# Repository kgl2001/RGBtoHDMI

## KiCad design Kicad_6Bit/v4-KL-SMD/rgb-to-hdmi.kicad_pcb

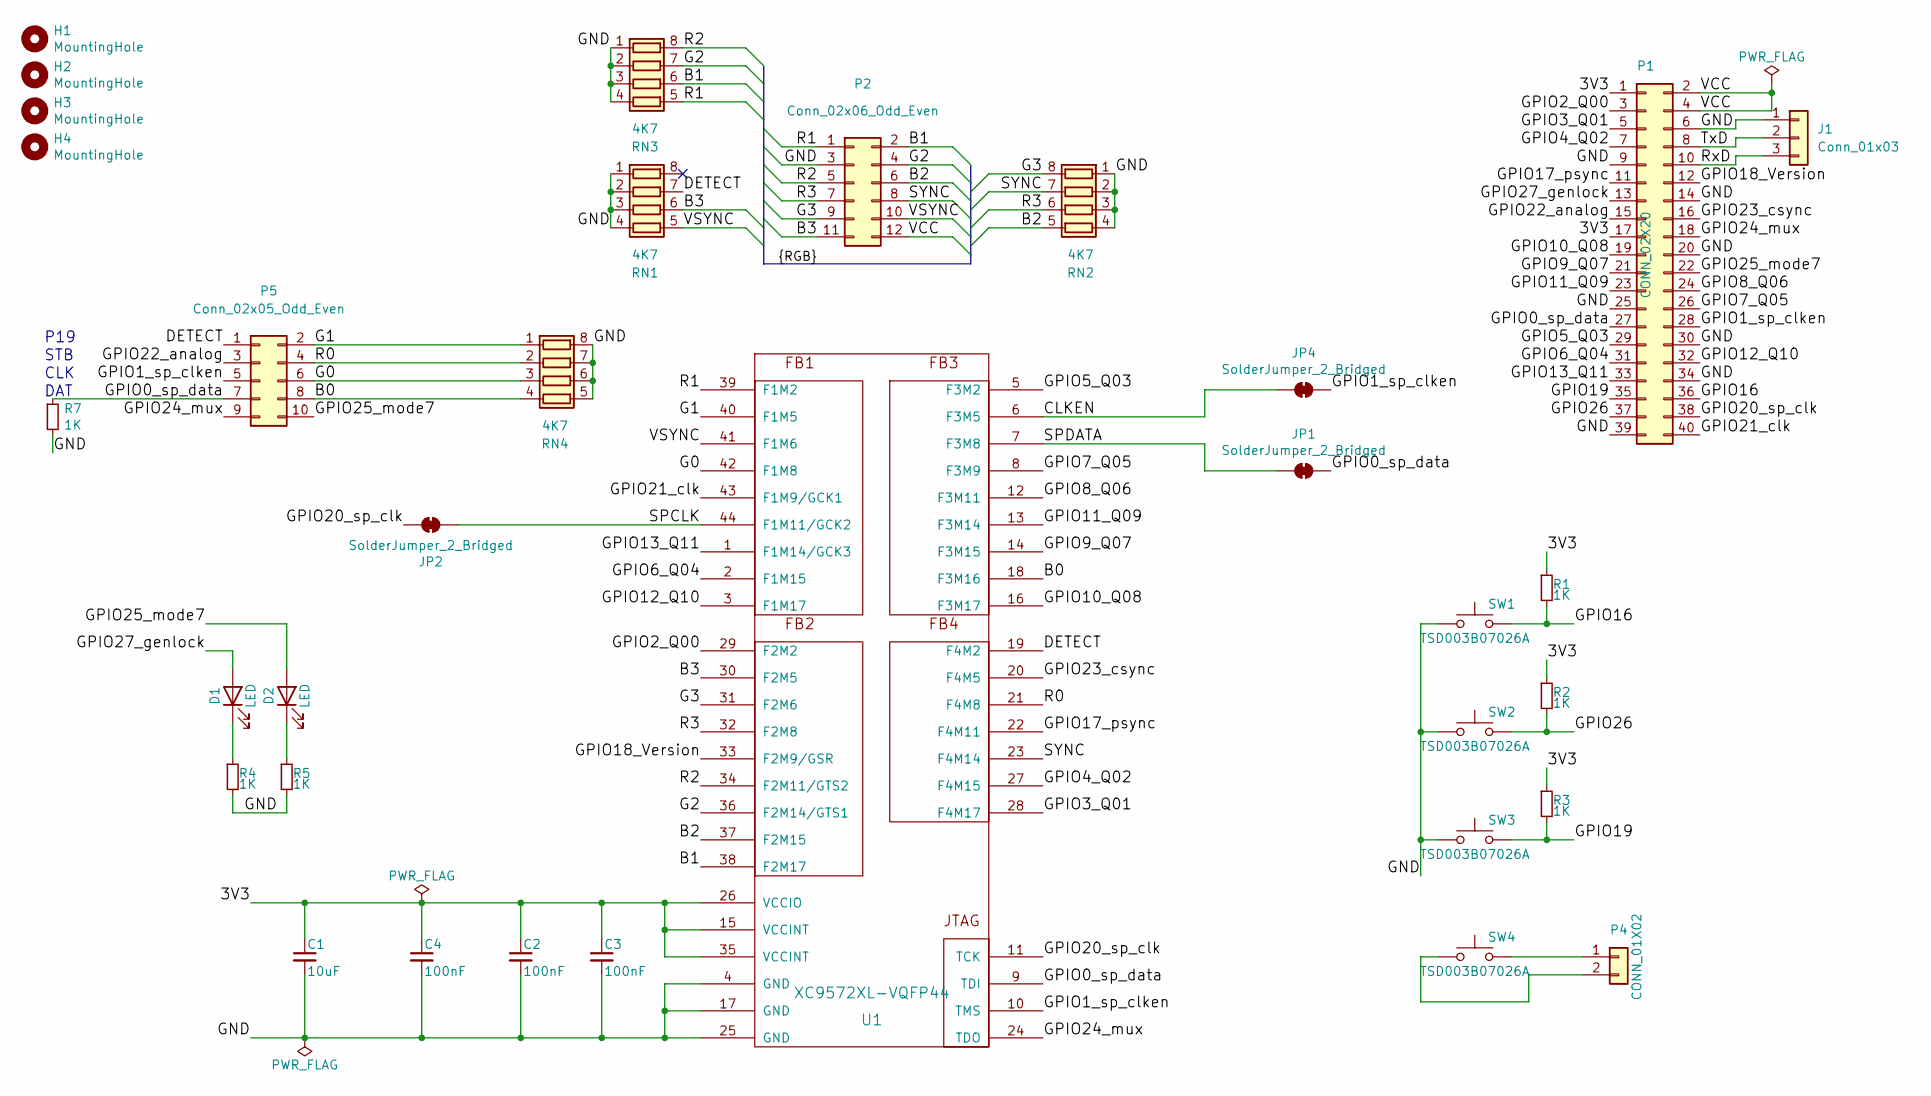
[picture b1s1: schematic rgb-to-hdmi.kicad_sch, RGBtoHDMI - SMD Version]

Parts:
C1: 10uF; C_0805_2012Metric; JLC Part Number C15850
C2, C3, C4: 100nF; C_0805_2012Metric; JLC Part Number C49678
D1, D2: LED; LED_0603_1608Metric; JLC Part Number C72043
H1, H2, H3, H4: MountingHole; MountingHole_2.7mm_M2.5_DIN965
J1: Conn_01x03; PinHeader_1x03_P2.54mm_Vertical
JP1, JP2, JP4: SolderJumper_2_Bridged; SolderJumper-2_P1.3mm_Bridged_RoundedPad1.0x1.5mm
P1: CONN_02X20; PinSocket_2x20_P2.54mm_Vertical
P2: Conn_02x06_Odd_Even; PinHeader_2x06_P2.54mm_Horizontal
P4: CONN_01X02; PinSocket_1x02_P2.54mm_Vertical
P5: Conn_02x05_Odd_Even; PinSocket_2x05_P2.54mm_Vertical
R1, R2, R3, R4, R5, R7: 1K; R_0603_1608Metric; JLC Part Number C21190
RN1, RN2, RN3, RN4: 4K7; R_Array_Concave_4x0603; JLC Part Number C1980
SW1, SW2, SW3, SW4: TSD003B07026A; SW_SPST_PTS645; JLC Part Number C2888790
U1: XC9572XL-VQFP44; LQFP-44_10x10mm_P0.8mm; JLC Part Number C569042

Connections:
/3V3: C1.1, C2.1, C3.1, C4.1, P1.1, P1.17, R1.1, R2.1, R3.1, U1.15 (VCCINT), U1.26 (VCCIO), U1.35 (VCCINT)
/B0: P5.8, RN4.4 (R4.1), U1.18 (F3M16)
/B1: P2.2, RN3.6 (R3.2), U1.38 (F2M17)
/B2: P2.6, RN2.5 (R4.2), U1.37 (F2M15)
/B3: P2.11, RN1.6 (R3.2), U1.30 (F2M5)
/CLKEN: JP4.2 (B), U1.6 (F3M5)
/DETECT: P5.1, RN1.7 (R2.2), U1.19 (F4M2)
/G0: P5.6, RN4.3 (R3.1), U1.42 (F1M8)
/G1: P5.2, RN4.1 (R1.1), U1.40 (F1M5)
/G2: P2.4, RN3.7 (R2.2), U1.36 (F2M14/GTS1)
/G3: P2.9, RN2.8 (R1.2), U1.31 (F2M6)
/GND: C1.2, C2.2, C3.2, C4.2, J1.1, P1.6, P1.9, P1.14, P1.20, P1.25, P1.30, P1.34, P1.39, P2.3, R4.2, R5.2, R7.2, RN1.1 (R1.1), RN1.2 (R2.1), RN1.3 (R3.1), RN1.4 (R4.1), RN2.1 (R1.1), RN2.2 (R2.1), RN2.3 (R3.1), RN2.4 (R4.1), RN3.1 (R1.1), RN3.2 (R2.1), RN3.3 (R3.1), RN3.4 (R4.1), RN4.5 (R4.2), RN4.6 (R3.2), RN4.7 (R2.2), RN4.8 (R1.2), SW1.1, SW2.1, SW3.1, U1.4 (GND), U1.17 (GND), U1.25 (GND)
/GPIO0_sp_data: JP1.1 (A), P1.27, P5.7, R7.1, U1.9 (TDI)
/GPIO1_sp_clken: JP4.1 (A), P1.28, P5.5, U1.10 (TMS)
/GPIO2_Q00: P1.3, U1.29 (F2M2)
/GPIO3_Q01: P1.5, U1.28 (F4M17)
/GPIO4_Q02: P1.7, U1.27 (F4M15)
/GPIO5_Q03: P1.29, U1.5 (F3M2)
/GPIO6_Q04: P1.31, U1.2 (F1M15)
/GPIO7_Q05: P1.26, U1.8 (F3M9)
/GPIO8_Q06: P1.24, U1.12 (F3M11)
/GPIO9_Q07: P1.21, U1.14 (F3M15)
/GPIO10_Q08: P1.19, U1.16 (F3M17)
/GPIO11_Q09: P1.23, U1.13 (F3M14)
/GPIO12_Q10: P1.32, U1.3 (F1M17)
/GPIO13_Q11: P1.33, U1.1 (F1M14/GCK3)
/GPIO16: P1.36, R1.2, SW1.2
/GPIO17_psync: P1.11, U1.22 (F4M11)
/GPIO18_Version: P1.12, U1.33 (F2M9/GSR)
/GPIO19: P1.35, R3.2, SW3.2
/GPIO20_sp_clk: JP2.1 (A), P1.38, U1.11 (TCK)
/GPIO21_clk: P1.40, U1.43 (F1M9/GCK1)
/GPIO22_analog: P1.15, P5.3
/GPIO23_csync: P1.16, U1.20 (F4M5)
/GPIO24_mux: P1.18, P5.9, U1.24 (TDO)
/GPIO25_mode7: D2.2 (A), P1.22, P5.10
/GPIO26: P1.37, R2.2, SW2.2
/GPIO27_genlock: D1.2 (A), P1.13
/R0: P5.4, RN4.2 (R2.1), U1.21 (F4M8)
/R1: P2.1, RN3.5 (R4.2), U1.39 (F1M2)
/R2: P2.5, RN3.8 (R1.2), U1.34 (F2M11/GTS2)
/R3: P2.7, RN2.6 (R3.2), U1.32 (F2M8)
/RxD: J1.3, P1.10
/SPCLK: JP2.2 (B), U1.44 (F1M11/GCK2)
/SPDATA: JP1.2 (B), U1.7 (F3M8)
/SYNC: P2.8, RN2.7 (R2.2), U1.23 (F4M14)
/TxD: J1.2, P1.8
/VCC: P1.2, P1.4, P2.12
/VSYNC: P2.10, RN1.5 (R4.2), U1.41 (F1M6)
unnamed: D1.1 (K), R4.1
unnamed: D2.1 (K), R5.1
unnamed: P4.1, SW4.2
unnamed: P4.2, SW4.1

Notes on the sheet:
P19
DAT
CLK
STB

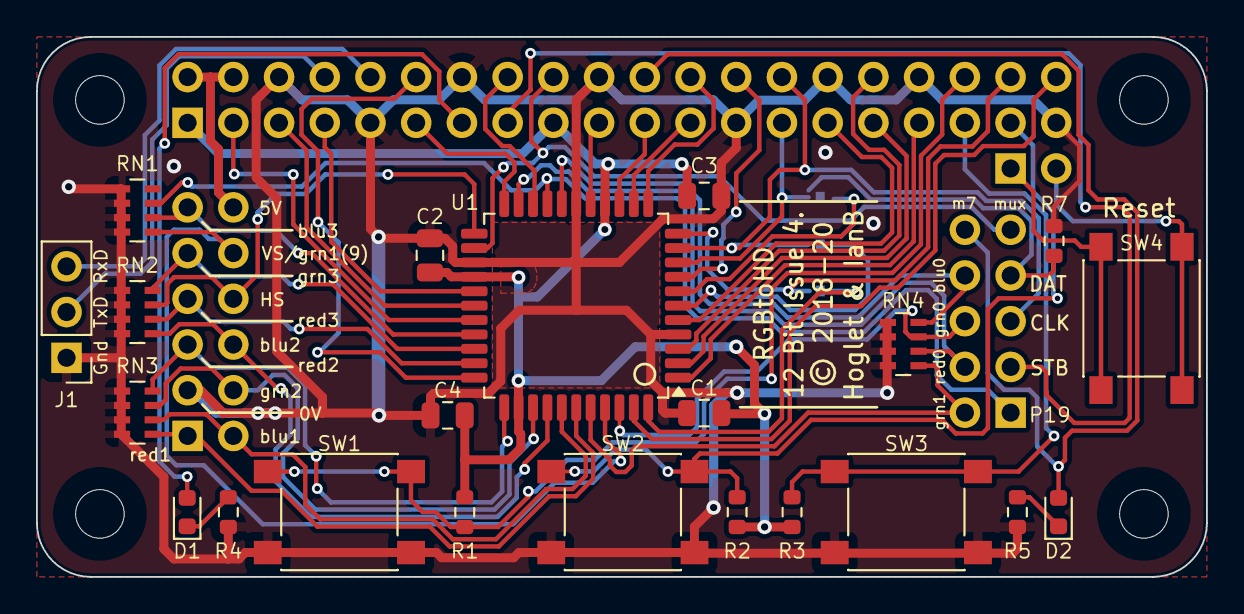
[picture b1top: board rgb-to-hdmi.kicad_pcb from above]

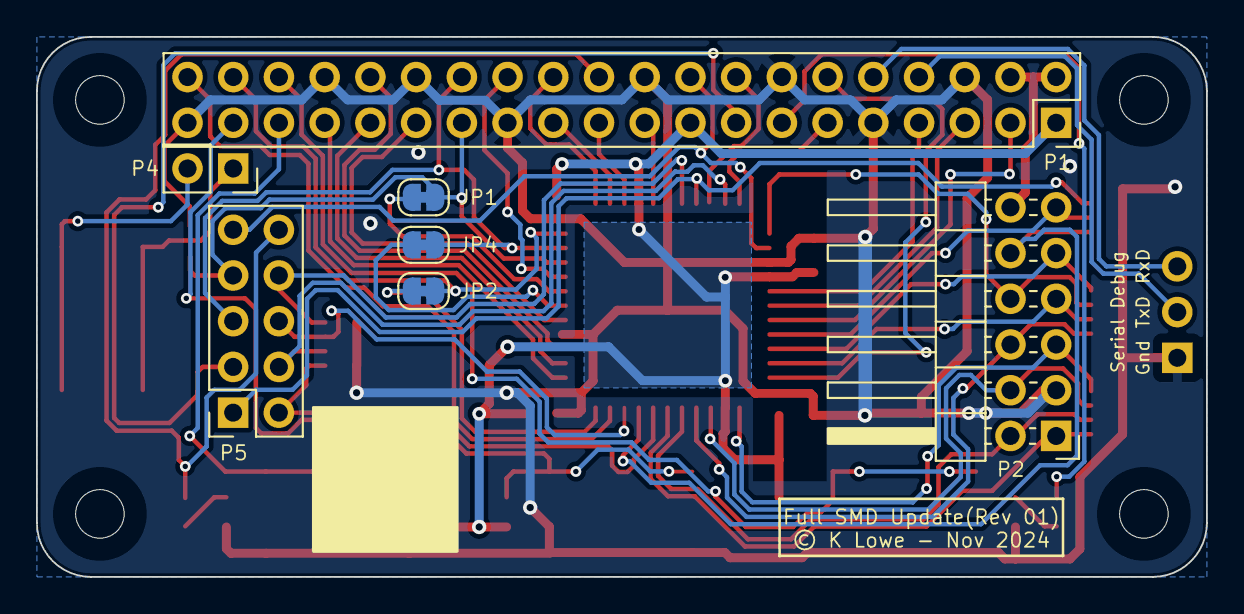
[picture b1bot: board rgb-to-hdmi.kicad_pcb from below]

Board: 2 copper layers, 65.0 x 30.0 mm, 33 parts (7 on the bottom side), 53 nets.

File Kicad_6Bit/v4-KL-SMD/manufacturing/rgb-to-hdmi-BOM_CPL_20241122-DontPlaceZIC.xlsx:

Designator | LCSC Part # | Footprint | JLCValue | Mid X | Mid Y | Rot | Side | Val | Package
C1 | C15850 | 0805 | 10uF | 53.073999999999998 | -45.39996 | 180 | top | 10uF | C_0805_2012Metric
C2 | C49678 | 0805 | 100nF | 37.834000000000003 | -36.636960000000002 | 90 | top | 100nF | C_0805_2012Metric
C3 | C49678 | 0805 | 100nF | 53.073999999999998 | -33.334960000000002 | 0 | top | 100nF | C_0805_2012Metric
C4 | C49678 | 0805 | 100nF | 38.819600000000001 | -45.526960000000003 | 180 | top | 100nF | C_0805_2012Metric
D1 | C72043 | LED_0603 | Green | 24.349 | -50.900959999999998 | 90 | top | LED | LED_0603_1608Metric
D2 | C72043 | LED_0603 | Green | 72.759 | -50.900959999999998 | 90 | top | LED | LED_0603_1608Metric
R1 | C21190 | 0603 | 1K | 39.769599999999997 | -50.900959999999998 | -90 | top | 1K | R_0603_1608Metric
R2 | C21190 | 0603 | 1K | 54.904000000000003 | -50.900959999999998 | 90 | top | 1K | R_0603_1608Metric
R3 | C21190 | 0603 | 1K | 57.951999999999998 | -50.900959999999998 | 90 | top | 1K | R_0603_1608Metric
R4 | C21190 | 0603 | 1K | 26.635000000000002 | -50.900959999999998 | -90 | top | 1K | R_0603_1608Metric
R5 | C21190 | 0603 | 1K | 70.472999999999999 | -50.900959999999998 | -90 | top | 1K | R_0603_1608Metric
R7 | C21190 | 0603 | 1K | 72.507660000000001 | -35.836860000000001 | 90 | top | 1K | R_0603_1608Metric
RN1 | C1980 | 0603_x4 | 4K7 | 21.583200000000001 | -34.141559999999998 | 270 | top | 4K7 | R_Array_Concave_4x0603
RN2 | C1980 | 0603_x4 | 4K7 | 21.583200000000001 | -39.786560000000001 | 270 | top | 4K7 | R_Array_Concave_4x0603
RN3 | C1980 | 0603_x4 | 4K7 | 21.583200000000001 | -45.374560000000002 | 270 | top | 4K7 | R_Array_Concave_4x0603
RN4 | C1980 | 0603_x4 | 4K7 | 64.128200000000007 | -41.56456 | 90 | top | 4K7 | R_Array_Concave_4x0603
SW1 | C2888790 | SMD | TSD003B07026A | 32.805999999999997 | -50.89696 | 180 | top | TSD003B07026A | SW_Push_1P1T_NO_6x6mm_H9.5mm
SW2 | C2888790 | SMD | TSD003B07026A | 48.554000000000002 | -50.89696 | 180 | top | TSD003B07026A | SW_Push_1P1T_NO_6x6mm_H9.5mm
SW3 | C2888790 | SMD | TSD003B07026A | 64.302000000000007 | -50.89696 | 180 | top | TSD003B07026A | SW_Push_1P1T_NO_6x6mm_H9.5mm
SW4 | C2888790 | SMD | TSD003B07026A | 77.367000000000004 | -40.14096 | -90 | top | TSD003B07026A | SW_Push_1P1T_NO_6x6mm_H9.5mm
U1 | C569042 | LQFP-44_10x10mm_P0.8mm | XC9572XL-VQFP44 | 45.962000000000003 | -39.430959999999999 | 90 | top | XC9572XL-VQFP44 | LQFP-44_10x10mm_P0.8mm
ZIC1 | C6082 | TSSOP-20_4.4x6.5x0.65P | 74LVC245 | 197.48500000000001 | -118.745 | 270 | top | 74LVC245 | TSSOP-20_4.4x6.5mm_P0.65mm
ZIC2 | C6082 | TSSOP-20_4.4x6.5x0.65P | 74LVC245 | 197.48500000000001 | -135.255 | 270 | top | 74LVC245 | TSSOP-20_4.4x6.5mm_P0.65mm
ZIC3 | C6082 | TSSOP-20_4.4x6.5x0.65P | 74LVC245 | 197.48500000000001 | -151.13 | 270 | top | 74LVC245 | TSSOP-20_4.4x6.5mm_P0.65mm
ZIC4 | C6082 | TSSOP-20_4.4x6.5x0.65P | 74LVC245 | 150.495 | -41.91 | 270 | top | 74LVC245 | TSSOP-20_4.4x6.5mm_P0.65mm

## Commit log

2025-06-27 Update design to use more SMD parts
2025-06-27 Add pdf schematic

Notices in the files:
Kicad_6Bit/v4-KL-SMD/rgb-to-hdmi.kicad_pcb:
© 2018-20
© K Lowe - Nov 2024
